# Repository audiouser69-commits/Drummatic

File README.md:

# Drummatic 0.4.0 — drum synth a 8 voci

Standalone per Windows (`Drummatic.exe` / `Drummatic.app`) e plugin VST3 (`Drummatic.vst3`) per Windows e macOS dallo stesso codice JUCE.
Architettura modellata sulle funzioni di una drum machine ibrida synth/sampler con sequencer euclideo;
nome, grafica e codice sono originali.

## Installazione
- **Standalone**: copia `Drummatic.exe` dove vuoi e avvialo. In *Options → Audio/MIDI Settings* scegli scheda audio
  (WASAPI/DirectSound) e, se vuoi, l'ingresso MIDI.
- **VST3 Windows**: copia `Drummatic.vst3` in `C:\Program Files\Common Files\VST3\` e riesegui la scansione in Ableton.
- **macOS**: `Drummatic.vst3` in `~/Library/Audio/Plug-Ins/VST3/`, `Drummatic.app` in Applicazioni; al primo avvio
  `xattr -dr com.apple.quarantine ~/Library/Audio/Plug-Ins/VST3/Drummatic.vst3 /Applications/Drummatic.app`.
- Preset, kit, campioni e WAV esportati vengono salvati in `Documenti/Drummatic/` (`Kits`, `Voices`, `Samples`, `Renders`); i file di `Documenti/Manipolo` vengono copiati lì al primo avvio.
  Con il pulsante **CARTELLA** nella barra superiore puoi scegliere un'altra cartella (anche un disco esterno), con la copia facoltativa dei file esistenti.
- Manuale completo: `docs/Drummatic-Manuale.pdf`.

## Funzioni
**Voce (×8)**
- Synth con 25 motori: Kick, Snare, Hat, Clap, FM, Modal, Cowbell, Zap, Pillow, Tripwire, Radiator, Kombucha
  (Karplus-Strong), LPG, Builder, Additive, Chaos, VOSIM, SumSyn, Reson, Combinatoric, Terraining, Shame, Entangled,
  Haywire, Scrapyard — PITCH + 4 manopole specifiche, ENV 2 come sorgente d'ampiezza, STEREO.
- Sampler con 4 motori: Classic (FINE, TILT, COMP, GAIN), Phase Warp (MIRROR, SHAPE, SPLIT, SWING),
  Cloner (FINE, TILT, VARIATION, DAMP — ogni colpo leggermente diverso; realizzato con un banco di 8 bande),
  Granular (SIZE, RATE, SPEED, BLUR). START/END trascinabili (END prima di START = reverse),
  drag & drop di WAV/AIFF/FLAC/OGG/MP3, file precedente/successivo/casuale nella cartella.
- BLEND synth/sampler (al 50% entrambi al massimo).
- TONE: 11 filtri (Scream/Dark LP-HP-BP, Comb FB±, FF±, AP), 11 distorsioni (Tape, Tube, Bitcrush, Rate Crush,
  Wavefold, Phase, Square, Dropout, MiniGlitch, MegaGlitch, Contrast), POST.
- Modulazione: RANDOM, VELOCITY, MACRO 1/2, ENV 1/2, LFO 1/2. Premi **MAP** su una sorgente e trascina le manopole
  per la profondità (doppio clic azzera). Tasto destro su una manopola = **lucchetto** (esclusa da VARIATION,
  randomizzazione e cambio preset). Alt+clic = valore di default.
- 2 inviluppi AHD (curva, velocity, soft reset), 2 LFO (Wavetable/Triangle Tilt/Pulse/Smooth Random,
  5 modalità di reset, sync o Hz fino a 440 Hz).
- VARIATION, mandate Delay/Reverb, PAN, VOICE GAIN; preset di voce, RESET, DADO.

**Sequencer per voce**
- Generatore euclideo STEPS/FILL/PATTERN (permutazioni)/ROTATE/INVERT + trigger manuali.
- SHIFT, SWING, SHAPE (accelera/rallenta), DENSITY; SPEED × MULT, LENGTH, SNAP, RESET; HUMANIZE globale condiviso.
- Lane per passo: VEL (127 = spinta extra di distorsione), SHIFT, PITCH, RATCH, ENV, PAN, VAR, PROB, SENDS, MACRO 2,
  ognuna con SYNC/FREE/TRIG/RETRIG e lunghezza propria; X, ruota ◀ ▶ (Alt = anche i trigger), DADO.
- Vista **ALL**: le sequenze delle 8 voci insieme, clic per aggiungere/togliere trigger, clic sul numero per selezionare la voce.
- Trasporto: segue il DAW, PLAY indipendente, STOP. In standalone usa il tempo in alto (BPM).
  Quando il DAW parte, il sequencer si riarma sempre, anche dopo uno STOP del plugin.

**Performance**
- ENV, SYNTH, SAMPLER, MODULATION (Macro 1/2, Variation, MOD AMP), TONE e SEQUENCER (Steps, Fill, Pattern, Density,
  Prob, Ratchet) agiscono su tutte le voci insieme.
- Per voce ENABLE e FLIP; GLOBAL con DEPTH bipolare, DADO (con profondità propria), COMMIT, RESET, ENABLED.
- Tasto destro su una manopola Performance la esclude dal DADO; i lucchetti delle voci la escludono dalla Performance.

**Mixer / FX / Master**
- Strip per voce con DELAY, REVERB, PAN, GAIN, TRIGGER (catena), CHOKE, ROUTING, Mute/Solo.
- **Uscite multiple**: Main 1-2 + 7 coppie stereo (3-4 … 15-16). In Ableton attiva le uscite del plugin e crea tracce
  audio con ingresso da Manipolo. Il MASTER agisce solo sul Main; le mandate FX escono sempre dal Main.
- Shatter Delay (tempo istantaneo senza glissati, GLITCH, STEREO, PONG, DUCKING, FB TILT, S.RATE, mandata al riverbero).
- Headspace Reverb (FDN, 4 modi, PREDELAY sync, DECAY, S.RATE, IN/OUT TILT).
- Master: MAXIMIZE, EQ 3 bande, Soft/Hard/Wavefold/No clip, GAIN.

**MIDI** (come da specifica)
- Ch 1: Do…Sol (qualsiasi ottava) = voci 1–8 · Ch 2–9: cromatico per voce (C3/60 = intonazione base)
- Ch 10: 0 play/stop, 1 play, 2 stop, 12–19 mute, 24–31 solo, 36–43 mute momentaneo, 48–55 solo momentaneo, 60–67 choke
- Ch 11: 0/1 kit prec./succ., 2 kit casuale, 3 randomizza tutto, 12 dado Performance, 13 reset Performance,
  14 commit Performance, 24–31 randomizza voce

**Tastiera** (pulsante TASTI attivo e finestra a fuoco): Q suona la voce, W/S voce su/giù, A/D pagina (VOICE/SEQ/MIX/PERFORM);
Spazio play/stop solo nello standalone. Nel DAW TASTI è spento di default, così spazio e tastiera MIDI del computer restano al DAW.
Shift+clic o doppio clic su una voce a sinistra = ascolto.

## Novità 0.4.0 — LAZER e performance di glitch programmate
**Cartella dei file selezionabile**: pulsante CARTELLA nella barra superiore (scegli, apri, torna a Documenti/Drummatic); copia facoltativa di kit, preset, campioni e WAV, con i percorsi dei campioni aggiornati nei kit copiati. Vale per standalone e plugin.

**Pagina LAZER** (nuova scheda, per la voce selezionata)
- Terzo strato sonoro accanto a synth e sampler: **64 motori glitch in 16 famiglie** — FM Metals, Laser Sweeps,
  Wavefold Zaps, Grain Clouds, Sub Thumps, Bit Zaps, Ring Mods, Noise Bursts, Comb Pings, Chirps, Formants,
  Glitch Steps, Data Corrupt, Phase Distort, Shimmer Drones, Static & Radio (4 varianti ciascuna).
- **12 manopole condivise** da tutti i motori (TUNE, SWEEP, S.TIME, TIMBRE, COLOR, MOD, RATE, GRIT, DENSITY, SPREAD,
  DECAY, LEVEL): ogni motore le interpreta a modo suo. Sono modulabili con MAP come le altre (LFO, inviluppi, macro,
  random, velocity), bloccabili e toccate da VARIATION e dal DADO.
- **Tappeti di fondo**: Grain Clouds, Shimmer Drones, Static & Radio e il Bowed Ping non ripartono da zero a ogni
  colpo; il tasto **ATMOSFERA** sceglie un motore di fondo con coda lunga e larga, da mettere sotto i glitch.
- Inviluppo proprio (DECAY fino a 20 s) oppure ENV 1 / ENV 2 della voce. Lo strato passa nel TONE della voce.
- **TAIL**: coda aggiunta a ogni colpo, 9 tipi (Bell, Metal, String, 808 Boom, Glass, Tube, Drone Pad, Noise Wash,
  Reverse Swell) con LEVEL, DECAY, TONE.
- **BRK TAPZ**: multi-tap fino a 32 ripetizioni; SHAPE accelera o rallenta i colpi (pallina che rimbalza), DECAY,
  SPREAD stereo, MIX, tempo sincronizzato o in ms.
- **BRK REPEAT**: stutter che registra una fetta del colpo e la ripete (REPEATS) con buchi casuali (GAPS), reverse
  e bitcrush casuali (CRUSH): fill spezzati.
- **KIT MODE**: sul canale MIDI della voce (2-9) ogni tasto suona un motore diverso (nota 36, C1 in Ableton = motore 1).
- **TRASCINA WAV**: trascina il colpo della voce direttamente nel DAW come file WAV (clic = salva nella
  cartella `Renders` di Drummatic).

**Sequencer della Performance** (pagina PERFORM)
- Fino a 64 passi a tempo col trasporto (durata del passo da 1/1 a 1/32T). Ogni passo può **bloccare** qualsiasi
  controllo Performance su un valore: è una scena programmata che cambia battuta dopo battuta.
- Nuovi controlli Performance per i glitch: LAZER (LEVEL, ENGINE, TIMBRE, COLOR, DENSITY, DECAY) e BRK (TZ MIX,
  TZ SHAPE, RPT MIX, GAPS, REVERSE, CRUSH). Un valore positivo su LEVEL / TZ MIX / RPT MIX **accende lo strato**
  anche nelle voci dove è spento: così un passo può far partire uno stutter o un laser solo lì.
- Per passo: **GLIDE** (scivola dalla scena precedente) e **PROB** (probabilità che il passo scatti).
- **REC**: in riproduzione i movimenti delle manopole vengono scritti nel passo che suona. **CATTURA** scrive le
  manopole nel passo selezionato; **Disegna**: scegli un controllo e disegna i valori passo per passo (Alt+clic
  toglie il blocco, tasto destro cancella il passo). **DADO GLITCH** genera una performance casuale (rispetta i
  lucchetti delle manopole).
- La sequenza si salva nel kit. Kit e preset delle versioni precedenti si caricano con lo strato LAZER spento.

**Hardware (Raspberry Pi)**: pagina VOICE con 4 banchi in più (LAZER 1/2, CODA E TAPZ, REPEAT) e pagina PERF con i
banchi GLITCH e GLITCH E SEQ. Il firmware FM-1 resta per ora alla versione precedente.

## Drummatic per M-VAVE FM-1
La cartella [`fm1/`](fm1/README.md) contiene Drummatic come **firmware per l'M-VAVE FM-1** (tutto tranne il sampler e
le uscite multiple: 8 voci, 25 motori, TONE, inviluppi, LFO, modulazione MAP, sequencer euclideo con le 10 lane,
Performance, delay, riverbero, master, MIDI) e un **emulatore nel browser** con lo stesso codice. Licenza GPL-3.0
(la piattaforma FM-1 viene da Felucca). Build: workflow *FM-1* di GitHub Actions (pacchetto `.fwsc`, emulatore,
Flasher per Windows).

## Drummatic hardware (Raspberry Pi 5) — novità 0.3.0
- Nuova app a schermo intero `drummatic-hw` per la macchina: Raspberry Pi 5 + Pisound + Touch Display 2 + circuito di controllo
  (cartella `hardware/`). Stesso motore audio del plugin.
- Il circuito "Drummatic Control" (USB-MIDI, canale 16) comanda 8 pagine (VOICE, SAMPLER, TONE, MOD, SEQ, LANE, MIX, PERF),
  8 encoder con banchi (frecce sinistra/destra), DATA, 16 tasti di passo, 8 tasti voce, trasporto, MAP, LOCK, DADO,
  COMMIT, KIT, COPY; i LED mostrano pagina, voce, passi e testina.
- Installazione: pacchetto `Drummatic-SD` (Raspberry Pi OS Lite 64 bit trixie + cartella `drummatic` sulla partizione bootfs),
  aggiornamenti, campioni e backup da chiavetta USB.
- Compilare: `cmake -S . -B build-a64 -G Ninja -DCMAKE_TOOLCHAIN_FILE=aarch64-toolchain.cmake -DDRUMMATIC_HW=ON`
  (sysroot con alsa-lib e freetype per aarch64), oppure nativo su Linux con `-DDRUMMATIC_HW=ON`.
  `DrummaticHWTest` simula il pannello e salva le schermate di tutte le pagine.

## Novità 0.2.4
- Risolto: l'audio poteva sparire all'improvviso dopo aver avviato Drummatic con il suo PLAY. Bastava che il DAW
  segnalasse anche per un attimo di essere in riproduzione (o partisse e si fermasse) perché il plugin passasse a
  "segui il DAW": al successivo stop del DAW restava muto finché non si premeva di nuovo PLAY. Ora il PLAY del plugin
  vale finché non premi STOP: col DAW in riproduzione segue la sua posizione, col DAW fermo continua da solo.
- Autoriparazione: se un motore, un filtro, una distorsione, il delay, il riverbero o il master producono un valore
  non valido, quel blocco viene azzerato al volo invece di restare guasto e zittire tutto.
- Diagnosi sullo schermo: se il sequencer è fermo mentre il DAW suona, al posto del nome del kit compare il motivo
  ("FERMO: premuto STOP" oppure "FERMO: nota MIDI … sul canale 10") e, dopo un'autoriparazione, "AUDIO RIPRISTINATO".

## Novità 0.2.3
- START ed END del sampler modulabili in modalità MAP trascinando i marcatori sulla forma d'onda (es. lane MACRO 2 → START per affettare un loop).
- Tempi visualizzati in modo pulito ("50 ms").
- Manuale: nuovo capitolo "Il sampler in pratica" con schermate annotate, grafici dei motori e sei tecniche.

## Novità 0.2.2
- Nuovo nome Drummatic, versione macOS universale, cartella utente `Documenti/Drummatic` con migrazione automatica.
- Corretta l'evidenziazione delle pagine nella barra superiore.

## Novità 0.2.1
- Risolto: l'audio poteva sparire durante la riproduzione nel DAW. Con la finestra del plugin attiva, lo spazio
  (e i tasti A/W/S/D della tastiera MIDI di Ableton) venivano catturati da Manipolo, che fermava il proprio sequencer.
  Ora i tasti restano al DAW e il play del DAW riarma comunque il sequencer.
- Un nuovo colpo annulla un CHOKE ancora in corso sulla stessa voce (prima poteva restare attenuata per un attimo).
- Distorsioni azzerate quando una voce riparte dal silenzio (Dropout non può più restare bloccato).
- Il DADO di voce/RANDOM non cambia più ROUTING ed ENABLE/FLIP della Performance (poteva mandare una voce
  su un'uscita ausiliaria non attiva, facendola sparire dal Main).
- Protezione contro blocchi audio più grandi di quelli annunciati dall'host.

## Limiti noti
- Driver **ASIO** non incluso nello standalone (l'SDK ASIO di Steinberg non è ridistribuibile): usa WASAPI in modalità
  esclusiva per una latenza bassa, oppure il VST3 dentro Ableton.
- La modulazione è calcolata ogni 16 campioni (≈0,3 ms): gli LFO fino a 440 Hz sono "audio-rate" solo in modo approssimato.
- Il Cloner usa un banco di filtri a 8 bande invece di una vera elaborazione FFT.
- Binari non firmati da un'autorità: Windows SmartScreen e macOS Gatekeeper mostrano un avviso al primo avvio.

## Compilare
Cross-compilazione da Linux: `cmake -S . -B build-win -G Ninja -DCMAKE_TOOLCHAIN_FILE=mingw-toolchain.cmake -DCMAKE_BUILD_TYPE=Release && cmake --build build-win`
(JUCE 7.0.12, scaricato automaticamente se manca la cartella `JUCE`). Su Windows funziona anche con Visual Studio 2022;
su macOS: `cmake -S . -B build -G Xcode -DCMAKE_OSX_ARCHITECTURES="arm64;x86_64" && cmake --build build --config Release`.
Test: `-DMANIPOLO_TESTS=ON` poi `ManipoloTest`.

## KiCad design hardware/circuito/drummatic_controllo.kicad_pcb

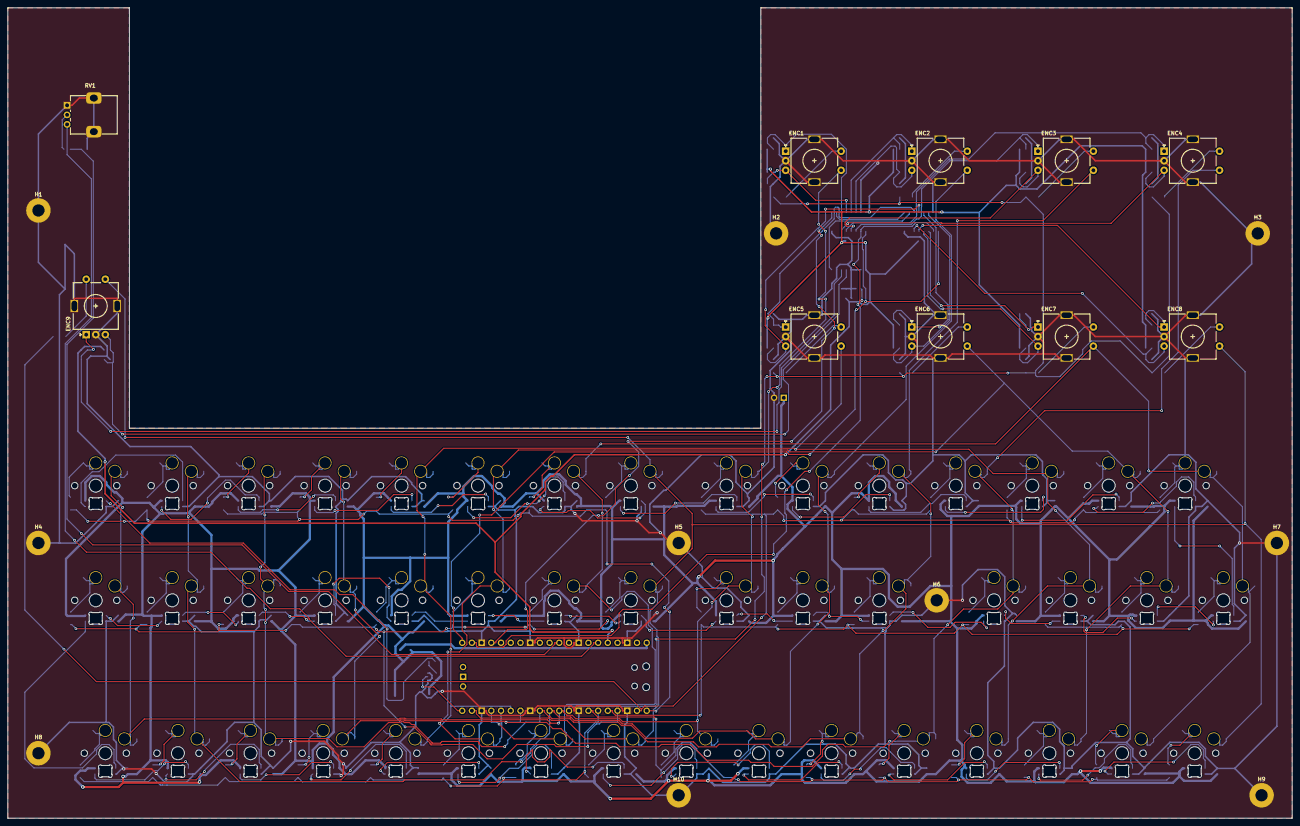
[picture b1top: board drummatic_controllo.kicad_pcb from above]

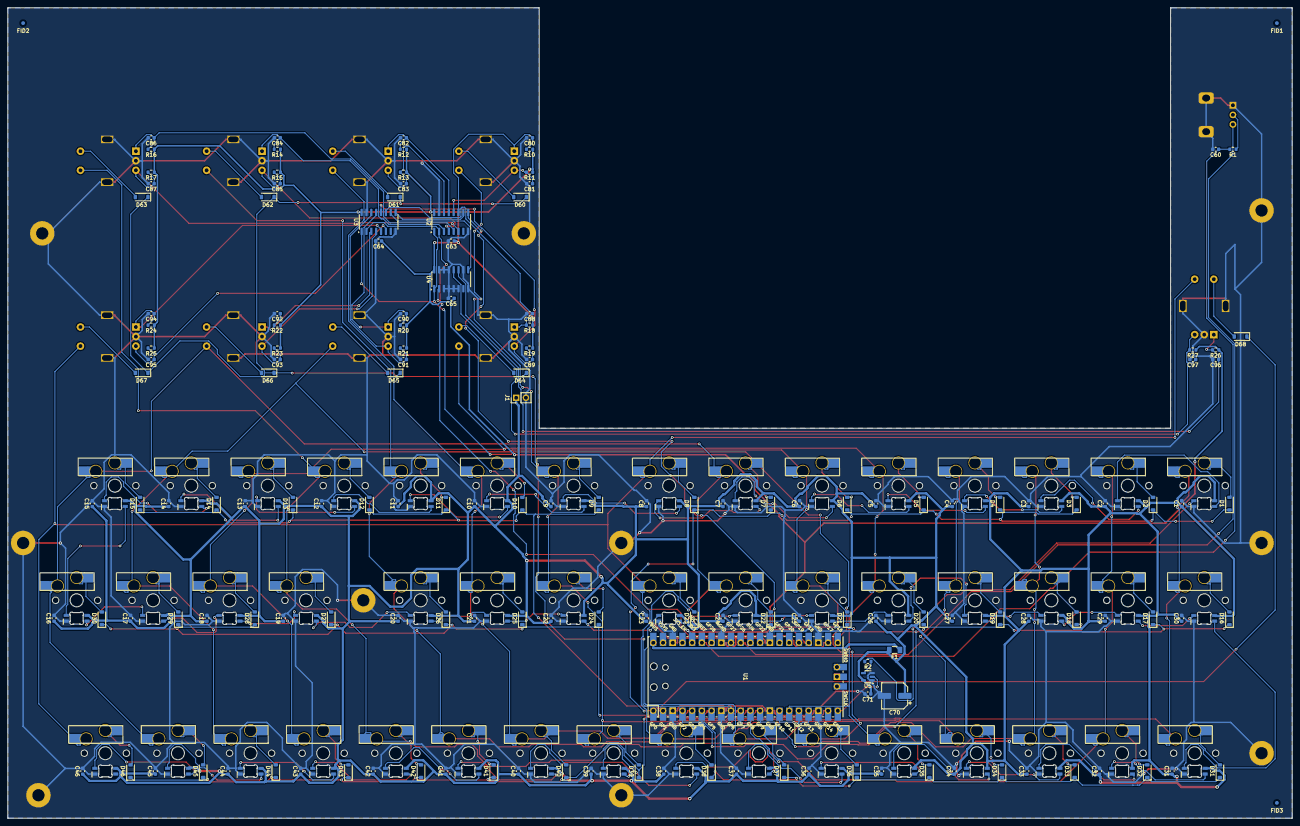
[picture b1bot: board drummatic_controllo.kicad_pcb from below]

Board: 2 copper layers, 336.0 x 212.0 mm, 267 parts (247 on the bottom side), 148 nets.

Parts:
C1, C2, C3, C4, C5, C6, C7, C8, C9, C10, C11, C12, C13, C14, C15, C16, C17, C18, C19, C20, C21, C22, C23, C24, C25, C26, C27, C28, C29, C30, C31, C32, C33, C34, C35, C36, C37, C38, C39, C40, C41, C42, C43, C44, C45, C46, C60, C63, C64, C65, C71: 100nF; C_0603_1608Metric
C70: 220uF 10V; CP_Elec_6.3x7.7
C80, C81, C82, C83, C84, C85, C86, C87, C88, C89, C90, C91, C92, C93, C94, C95, C96, C97: 10nF; C_0603_1608Metric
D1, D2, D3, D4, D5, D6, D7, D8, D9, D10, D11, D12, D13, D14, D15, D16, D17, D18, D19, D20, D21, D22, D23, D24, D25, D26, D27, D28, D29, D30, D31, D32, D33, D34, D35, D36, D37, D38, D39, D40, D41, D42, D43, D44, D45, D46, D60, D61, D62, D63, D64, D65, D66, D67, D68: 1N4148W; D_SOD-123
ENC1: EC11E ENC1; RotaryEncoder_Alps_EC11E-Switch_Vertical_H20mm
ENC2: EC11E ENC2; RotaryEncoder_Alps_EC11E-Switch_Vertical_H20mm
ENC3: EC11E ENC3; RotaryEncoder_Alps_EC11E-Switch_Vertical_H20mm
ENC4: EC11E ENC4; RotaryEncoder_Alps_EC11E-Switch_Vertical_H20mm
ENC5: EC11E ENC5; RotaryEncoder_Alps_EC11E-Switch_Vertical_H20mm
ENC6: EC11E ENC6; RotaryEncoder_Alps_EC11E-Switch_Vertical_H20mm
ENC7: EC11E ENC7; RotaryEncoder_Alps_EC11E-Switch_Vertical_H20mm
ENC8: EC11E ENC8; RotaryEncoder_Alps_EC11E-Switch_Vertical_H20mm
ENC9: EC11E DATA; RotaryEncoder_Alps_EC11E-Switch_Vertical_H20mm
F1: PTC 1.5A; Fuse_1206_3216Metric
FID1, FID2, FID3: Fiducial; Fiducial_1mm_Mask2mm
H1, H2, H3, H4, H5, H6, H7, H8, H9, H10: M3; MountingHole_3.2mm_M3_Pad
J1: DISPLAY 5V; PinHeader_1x02_P2.54mm_Vertical
LED1, LED2, LED3, LED4, LED5, LED6, LED7, LED8, LED9, LED10, LED11, LED12, LED13, LED14, LED15, LED16, LED17, LED18, LED19, LED20, LED21, LED22, LED23, LED24, LED25, LED26, LED27, LED28, LED29, LED30, LED31, LED32, LED33, LED34, LED35, LED36, LED37, LED38, LED39, LED40, LED41, LED42, LED43, LED44, LED45, LED46: SK6812MINI-E; SK6812MINI-E_Reverse
R1: 1k; R_0603_1608Metric
R2: 330R; R_0603_1608Metric
R10, R11, R12, R13, R14, R15, R16, R17, R18, R19, R20, R21, R22, R23, R24, R25, R26, R27: 10k; R_0603_1608Metric
RV1: 10k lin VOLUME; Potentiometer_Alps_RK09K_Single_Vertical
SW1: Choc v1 VOICE; Choc_v1_Hotswap
SW2: Choc v1 SMPL; Choc_v1_Hotswap
SW3: Choc v1 TONE; Choc_v1_Hotswap
SW4: Choc v1 MOD; Choc_v1_Hotswap
SW5: Choc v1 SEQ; Choc_v1_Hotswap
SW6: Choc v1 LANE; Choc_v1_Hotswap
SW7: Choc v1 MIX; Choc_v1_Hotswap
SW8: Choc v1 PERF; Choc_v1_Hotswap
SW9: Choc v1 FUNC; Choc_v1_Hotswap
SW10: Choc v1 MAP; Choc_v1_Hotswap
SW11: Choc v1 LOCK; Choc_v1_Hotswap
SW12: Choc v1 DADO; Choc_v1_Hotswap
SW13: Choc v1 COMMIT; Choc_v1_Hotswap
SW14: Choc v1 KIT; Choc_v1_Hotswap
SW15: Choc v1 COPY; Choc_v1_Hotswap
SW16: Choc v1 VOICE1; Choc_v1_Hotswap
SW17: Choc v1 VOICE2; Choc_v1_Hotswap
SW18: Choc v1 VOICE3; Choc_v1_Hotswap
SW19: Choc v1 VOICE4; Choc_v1_Hotswap
SW20: Choc v1 VOICE5; Choc_v1_Hotswap
SW21: Choc v1 VOICE6; Choc_v1_Hotswap
SW22: Choc v1 VOICE7; Choc_v1_Hotswap
SW23: Choc v1 VOICE8; Choc_v1_Hotswap
SW24: Choc v1 REC; Choc_v1_Hotswap
SW25: Choc v1 PLAY; Choc_v1_Hotswap
SW26: Choc v1 STOP; Choc_v1_Hotswap
SW27: Choc v1 LEFT; Choc_v1_Hotswap
SW28: Choc v1 UP; Choc_v1_Hotswap
SW29: Choc v1 DOWN; Choc_v1_Hotswap
SW30: Choc v1 RIGHT; Choc_v1_Hotswap
SW31: Choc v1 TRIG1; Choc_v1_Hotswap
SW32: Choc v1 TRIG2; Choc_v1_Hotswap
SW33: Choc v1 TRIG3; Choc_v1_Hotswap
SW34: Choc v1 TRIG4; Choc_v1_Hotswap
SW35: Choc v1 TRIG5; Choc_v1_Hotswap
SW36: Choc v1 TRIG6; Choc_v1_Hotswap
SW37: Choc v1 TRIG7; Choc_v1_Hotswap
SW38: Choc v1 TRIG8; Choc_v1_Hotswap
SW39: Choc v1 TRIG9; Choc_v1_Hotswap
SW40: Choc v1 TRIG10; Choc_v1_Hotswap
SW41: Choc v1 TRIG11; Choc_v1_Hotswap
SW42: Choc v1 TRIG12; Choc_v1_Hotswap
SW43: Choc v1 TRIG13; Choc_v1_Hotswap
SW44: Choc v1 TRIG14; Choc_v1_Hotswap
SW45: Choc v1 TRIG15; Choc_v1_Hotswap
SW46: Choc v1 TRIG16; Choc_v1_Hotswap
U1: Raspberry Pi Pico 2; RPi_Pico_SMD_TH
U2, U3, U4: 74HC165; SOIC-16_3.9x9.9mm_P1.27mm
U5: 74AHCT1G125; SOT-23-5

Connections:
+3V3: C63.1, C64.1, C65.1, R10.1, R11.1, R12.1, R13.1, R14.1, R15.1, R16.1, R17.1, R18.1, R19.1, R20.1, R21.1, R22.1, R23.1, R24.1, R25.1, R26.1, R27.1, U1.36, U2.16, U3.16, U4.16
+5V: C1.1, C2.1, C3.1, C4.1, C5.1, C6.1, C7.1, C8.1, C9.1, C10.1, C11.1, C12.1, C13.1, C14.1, C15.1, C16.1, C17.1, C18.1, C19.1, C20.1, C21.1, C22.1, C23.1, C24.1, C25.1, C26.1, C27.1, C28.1, C29.1, C30.1, C31.1, C32.1, C33.1, C34.1, C35.1, C36.1, C37.1, C38.1, C39.1, C40.1, C41.1, C42.1, C43.1, C44.1, C45.1, C46.1, C70.1, C71.1, F1.2, J1.1, LED1.1, LED2.1, LED3.1, LED4.1, LED5.1, LED6.1, LED7.1, LED8.1, LED9.1, LED10.1, LED11.1, LED12.1, LED13.1, LED14.1, LED15.1, LED16.1, LED17.1, LED18.1, LED19.1, LED20.1, LED21.1, LED22.1, LED23.1, LED24.1, LED25.1, LED26.1, LED27.1, LED28.1, LED29.1, LED30.1, LED31.1, LED32.1, LED33.1, LED34.1, LED35.1, LED36.1, LED37.1, LED38.1, LED39.1, LED40.1, LED41.1, LED42.1, LED43.1, LED44.1, LED45.1, LED46.1, U5.5
ADC0: C60.1, R1.2, U1.31
ADC_VREF: RV1.3, U1.35
COL0: ENC1.S1, SW1.1, SW9.1, SW16.1, SW24.1, SW31.1, SW39.1, U1.10
COL1: ENC2.S1, SW2.1, SW10.1, SW17.1, SW25.1, SW32.1, SW40.1, U1.11
COL2: ENC3.S1, SW3.1, SW11.1, SW18.1, SW26.1, SW33.1, SW41.1, U1.12
COL3: ENC4.S1, SW4.1, SW12.1, SW19.1, SW27.1, SW34.1, SW42.1, U1.14
COL4: ENC5.S1, SW5.1, SW13.1, SW20.1, SW28.1, SW35.1, SW43.1, U1.15
COL5: ENC6.S1, SW6.1, SW14.1, SW21.1, SW29.1, SW36.1, SW44.1, U1.16
COL6: ENC7.S1, SW7.1, SW15.1, SW22.1, SW30.1, SW37.1, SW45.1, U1.17
COL7: ENC8.S1, ENC9.S1, SW8.1, SW23.1, SW38.1, SW46.1, U1.19
DATA_A: C96.1, ENC9.A, R26.2, U4.11
DATA_B: C97.1, ENC9.B, R27.2, U4.12
ENC1_A: C80.1, ENC1.A, R10.2, U2.11
ENC1_B: C81.1, ENC1.B, R11.2, U2.12
ENC2_A: C82.1, ENC2.A, R12.2, U2.13
ENC2_B: C83.1, ENC2.B, R13.2, U2.14
ENC3_A: C84.1, ENC3.A, R14.2, U2.3
ENC3_B: C85.1, ENC3.B, R15.2, U2.4
ENC4_A: C86.1, ENC4.A, R16.2, U2.5
ENC4_B: C87.1, ENC4.B, R17.2, U2.6
ENC5_A: C88.1, ENC5.A, R18.2, U3.11
ENC5_B: C89.1, ENC5.B, R19.2, U3.12
ENC6_A: C90.1, ENC6.A, R20.2, U3.13
ENC6_B: C91.1, ENC6.B, R21.2, U3.14
ENC7_A: C92.1, ENC7.A, R22.2, U3.3
ENC7_B: C93.1, ENC7.B, R23.2, U3.4
ENC8_A: C94.1, ENC8.A, R24.2, U3.5
ENC8_B: C95.1, ENC8.B, R25.2, U3.6
GND: C1.2, C2.2, C3.2, C4.2, C5.2, C6.2, C7.2, C8.2, C9.2, C10.2, C11.2, C12.2, C13.2, C14.2, C15.2, C16.2, C17.2, C18.2, C19.2, C20.2, C21.2, C22.2, C23.2, C24.2, C25.2, C26.2, C27.2, C28.2, C29.2, C30.2, C31.2, C32.2, C33.2, C34.2, C35.2, C36.2, C37.2, C38.2, C39.2, C40.2, C41.2, C42.2, C43.2, C44.2, C45.2, C46.2, C60.2, C63.2, C64.2, C65.2, C70.2, C71.2, C80.2, C81.2, C82.2, C83.2, C84.2, C85.2, C86.2, C87.2, C88.2, C89.2, C90.2, C91.2, C92.2, C93.2, C94.2, C95.2, C96.2, C97.2, ENC1.C, ENC1.MP, ENC2.C, ENC2.MP, ENC3.C, ENC3.MP, ENC4.C, ENC4.MP, ENC5.C, ENC5.MP, ENC6.C, ENC6.MP, ENC7.C, ENC7.MP, ENC8.C, ENC8.MP, ENC9.C, ENC9.MP, H1.1, H2.1, H3.1, H4.1, H5.1, H6.1, H7.1, H8.1, H9.1, H10.1, J1.2, LED1.4, LED2.4, LED3.4, LED4.4, LED5.4, LED6.4, LED7.4, LED8.4, LED9.4, LED10.4, LED11.4, LED12.4, LED13.4, LED14.4, LED15.4, LED16.4, LED17.4, LED18.4, LED19.4, LED20.4, LED21.4, LED22.4, LED23.4, LED24.4, LED25.4, LED26.4, LED27.4, LED28.4, LED29.4, LED30.4, LED31.4, LED32.4, LED33.4, LED34.4, LED35.4, LED36.4, LED37.4, LED38.4, LED39.4, LED40.4, LED41.4, LED42.4, LED43.4, LED44.4, LED45.4, LED46.4, RV1.1, RV1.MP, U1.3, U1.8, U1.13, U1.18, U1.23, U1.28, U1.33, U1.38, U2.8, U2.15, U3.8, U3.15, U4.3, U4.4, U4.5, U4.6, U4.8, U4.10, U4.13, U4.14, U4.15, U5.1, U5.3
K1: D1.2, SW1.2
K2: D2.2, SW2.2
K3: D3.2, SW3.2
K4: D4.2, SW4.2
K5: D5.2, SW5.2
K6: D6.2, SW6.2
K7: D7.2, SW7.2
K8: D8.2, SW8.2
K9: D9.2, SW9.2
K10: D10.2, SW10.2
K11: D11.2, SW11.2
K12: D12.2, SW12.2
K13: D13.2, SW13.2
K14: D14.2, SW14.2
K15: D15.2, SW15.2
K16: D16.2, SW16.2
K17: D17.2, SW17.2
K18: D18.2, SW18.2
K19: D19.2, SW19.2
K20: D20.2, SW20.2
K21: D21.2, SW21.2
K22: D22.2, SW22.2
K23: D23.2, SW23.2
K24: D24.2, SW24.2
K25: D25.2, SW25.2
K26: D26.2, SW26.2
K27: D27.2, SW27.2
K28: D28.2, SW28.2
K29: D29.2, SW29.2
K30: D30.2, SW30.2
K31: D31.2, SW31.2
K32: D32.2, SW32.2
K33: D33.2, SW33.2
K34: D34.2, SW34.2
K35: D35.2, SW35.2
K36: D36.2, SW36.2
K37: D37.2, SW37.2
K38: D38.2, SW38.2
K39: D39.2, SW39.2
K40: D40.2, SW40.2
K41: D41.2, SW41.2
K42: D42.2, SW42.2
K43: D43.2, SW43.2
K44: D44.2, SW44.2
K45: D45.2, SW45.2
K46: D46.2, SW46.2
KE1: D60.2, ENC1.S2
KE2: D61.2, ENC2.S2
KE3: D62.2, ENC3.S2
KE4: D63.2, ENC4.S2
KE5: D64.2, ENC5.S2
KE6: D65.2, ENC6.S2
KE7: D66.2, ENC7.S2
KE8: D67.2, ENC8.S2
KE9: D68.2, ENC9.S2
LED_3V3: U1.20, U5.2
LED_5V: R2.1, U5.4
LED_D1: LED1.2, LED2.3
LED_D2: LED2.2, LED3.3
LED_D3: LED3.2, LED4.3
LED_D4: LED4.2, LED5.3
LED_D5: LED5.2, LED6.3
LED_D6: LED6.2, LED7.3
LED_D7: LED7.2, LED8.3
LED_D8: LED8.2, LED9.3
LED_D9: LED9.2, LED10.3
LED_D10: LED10.2, LED11.3
LED_D11: LED11.2, LED12.3
LED_D12: LED12.2, LED13.3
LED_D13: LED13.2, LED14.3
LED_D14: LED14.2, LED15.3
LED_D15: LED15.2, LED16.3
LED_D16: LED16.2, LED17.3
LED_D17: LED17.2, LED18.3
LED_D18: LED18.2, LED19.3
LED_D19: LED19.2, LED20.3
LED_D20: LED20.2, LED21.3
LED_D21: LED21.2, LED22.3
LED_D22: LED22.2, LED23.3
LED_D23: LED23.2, LED24.3
LED_D24: LED24.2, LED25.3
LED_D25: LED25.2, LED26.3
LED_D26: LED26.2, LED27.3
LED_D27: LED27.2, LED28.3
LED_D28: LED28.2, LED29.3
LED_D29: LED29.2, LED30.3
LED_D30: LED30.2, LED31.3
LED_D31: LED31.2, LED32.3
LED_D32: LED32.2, LED33.3
LED_D33: LED33.2, LED34.3
LED_D34: LED34.2, LED35.3
LED_D35: LED35.2, LED36.3
LED_D36: LED36.2, LED37.3
LED_D37: LED37.2, LED38.3
LED_D38: LED38.2, LED39.3
LED_D39: LED39.2, LED40.3
LED_D40: LED40.2, LED41.3
LED_D41: LED41.2, LED42.3
LED_D42: LED42.2, LED43.3
LED_D43: LED43.2, LED44.3
LED_D44: LED44.2, LED45.3
LED_D45: LED45.2, LED46.3
LED_DIN0: LED1.3, R2.2
POT_W: R1.1, RV1.2
ROW0: D1.1, D2.1, D3.1, D4.1, D5.1, D6.1, D7.1, D8.1, U1.1
ROW1: D9.1, D10.1, D11.1, D12.1, D13.1, D14.1, D15.1, D68.1, U1.2
ROW2: D16.1, D17.1, D18.1, D19.1, D20.1, D21.1, D22.1, D23.1, U1.4
ROW3: D24.1, D25.1, D26.1, D27.1, D28.1, D29.1, D30.1, U1.5
ROW4: D31.1, D32.1, D33.1, D34.1, D35.1, D36.1, D37.1, D38.1, U1.6
ROW5: D39.1, D40.1, D41.1, D42.1, D43.1, D44.1, D45.1, D46.1, U1.7
ROW6: D60.1, D61.1, D62.1, D63.1, D64.1, D65.1, D66.1, D67.1, U1.9
SR_CLK: U1.22, U2.2, U3.2, U4.2
SR_DATA: U1.24, U2.9
SR_LOAD: U1.21, U2.1, U3.1, U4.1
SR_S1: U2.10, U3.9
SR_S2: U3.10, U4.9
VBUS: F1.1, U1.40

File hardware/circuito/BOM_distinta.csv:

Quantità,Valore,Codice produttore,Footprint,Montaggio,Lato,Designatori
51,100nF,GRM188R71H104KA93D,C_0603_1608Metric,SMD,Bottom,C1 C2 C3 C4 C5 C6 C7 C8 C9 C10 C11 C12 C13 C14 C15 C16 C17 C18 C19 C20 C21 C22 C23 C24 C25 C26 C27 C28 C29 C30 C31 C32 C33 C34 C35 C36 C37 C38 C39 C40 C41 C42 C43 C44 C45 C46 C60 C63 C64 C65 C71
1,220uF 10V,Panasonic EEE-FK1A221P,CP_Elec_6.3x7.7,SMD,Bottom,C70
18,10nF,GRM188R71H103KA01D,C_0603_1608Metric,SMD,Bottom,C80 C81 C82 C83 C84 C85 C86 C87 C88 C89 C90 C91 C92 C93 C94 C95 C96 C97
55,1N4148W,1N4148W-7-F (Diodes Inc.),D_SOD-123,SMD,Bottom,D1 D2 D3 D4 D5 D6 D7 D8 D9 D10 D11 D12 D13 D14 D15 D16 D17 D18 D19 D20 D21 D22 D23 D24 D25 D26 D27 D28 D29 D30 D31 D32 D33 D34 D35 D36 D37 D38 D39 D40 D41 D42 D43 D44 D45 D46 D60 D61 D62 D63 D64 D65 D66 D67 D68
9,Encoder EC11E con pulsante,Alps EC11E15244G1 (o EC11E15244B2),RotaryEncoder_Alps_EC11E-Switch_Vertical_H20mm,THT,Top,ENC1 ENC2 ENC3 ENC4 ENC5 ENC6 ENC7 ENC8 ENC9
1,PTC 1.5A,Littelfuse 1206L150THYR,Fuse_1206_3216Metric,SMD,Bottom,F1
1,DISPLAY 5V,"Header 2 pin 2,54 mm",PinHeader_1x02_P2.54mm_Vertical,THT,Bottom,J1
46,SK6812MINI-E,SK6812MINI-E (Opsco),SK6812MINI-E_Reverse,SMD,Bottom,LED1 LED2 LED3 LED4 LED5 LED6 LED7 LED8 LED9 LED10 LED11 LED12 LED13 LED14 LED15 LED16 LED17 LED18 LED19 LED20 LED21 LED22 LED23 LED24 LED25 LED26 LED27 LED28 LED29 LED30 LED31 LED32 LED33 LED34 LED35 LED36 LED37 LED38 LED39 LED40 LED41 LED42 LED43 LED44 LED45 LED46
1,1k,RC0603FR-071KL,R_0603_1608Metric,SMD,Bottom,R1
1,330R,RC0603FR-07330RL,R_0603_1608Metric,SMD,Bottom,R2
18,10k,RC0603FR-0710KL,R_0603_1608Metric,SMD,Bottom,R10 R11 R12 R13 R14 R15 R16 R17 R18 R19 R20 R21 R22 R23 R24 R25 R26 R27
1,10k lin VOLUME,Alps RK09K1130A5R (10k B),Potentiometer_Alps_RK09K_Single_Vertical,THT,Top,RV1
46,Presa hot-swap Choc v1,Kailh CPG135001S30 (presa hot-swap),Choc_v1_Hotswap,SMD,Bottom,SW1 SW2 SW3 SW4 SW5 SW6 SW7 SW8 SW9 SW10 SW11 SW12 SW13 SW14 SW15 SW16 SW17 SW18 SW19 SW20 SW21 SW22 SW23 SW24 SW25 SW26 SW27 SW28 SW29 SW30 SW31 SW32 SW33 SW34 SW35 SW36 SW37 SW38 SW39 SW40 SW41 SW42 SW43 SW44 SW45 SW46
1,Raspberry Pi Pico 2,Raspberry Pi Pico 2 (SC1631),RPi_Pico_SMD_TH,SMD,Bottom,U1
3,74HC165,SN74HC165DR (TI),SOIC-16_3.9x9.9mm_P1.27mm,SMD,Bottom,U2 U3 U4
1,74AHCT1G125,SN74AHCT1G125DBVR (TI),SOT-23-5,SMD,Bottom,U5

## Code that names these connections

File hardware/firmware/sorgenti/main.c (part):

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
#define MIDI_CH      15          /* canale 16 */
#define FW_VERSION   2           /* 1 = 26/10/2026; 2 = 27/10/2026, aggiornabile via SysEx */
#define PIN_ROW0     0
#define PIN_COL0     7
#define PIN_LED      15
#define PIN_SR_LOAD  16
#define PIN_SR_CLK   17
#define PIN_SR_DATA  18
#define PIN_POT      26
#define MAX_LEVEL    51          /* 20 % del massimo: 46 LED bianchi ~0,35 A, così LED + display restano sotto 1 A dall'USB */

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
/* ---------------------------------------------------------------- matrice tasti */
static void matrix_init(void) {
    for (int r = 0; r < 7; r++) { gpio_init(PIN_ROW0 + r); gpio_set_dir(PIN_ROW0 + r, GPIO_IN); }
    for (int c = 0; c < 8; c++) { gpio_init(PIN_COL0 + c); gpio_set_dir(PIN_COL0 + c, GPIO_IN); gpio_pull_up(PIN_COL0 + c); }
}

static void matrix_scan(void) {
    for (int r = 0; r < 7; r++) {
        /* riga attiva = uscita bassa, le altre in alta impedenza; i diodi vanno da colonna a riga */
        gpio_set_dir(PIN_ROW0 + r, GPIO_OUT); gpio_put(PIN_ROW0 + r, 0);
        busy_wait_us_32(10);
        uint32_t cols = gpio_get_all();
        gpio_set_dir(PIN_ROW0 + r, GPIO_IN);
        for (int c = 0; c < 8; c++) {
            int k = MATRIX[r][c];
            if (k < 0) continue;
            bool pressed = !(cols & (1u << (PIN_COL0 + c)));
            if (pressed != key_state[k]) {
                if (++key_debounce[k] >= 5) {       /* 5 scansioni consecutive (~5 ms) */
                    key_state[k] = pressed; key_debounce[k] = 0;
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static const int8_t QDEC[16] = {0, -1, 1, 0, 1, 0, 0, -1, -1, 0, 0, 1, 0, 1, -1, 0};

static void sr_init(void) {
    gpio_init(PIN_SR_LOAD); gpio_set_dir(PIN_SR_LOAD, GPIO_OUT); gpio_put(PIN_SR_LOAD, 1);
    gpio_init(PIN_SR_CLK); gpio_set_dir(PIN_SR_CLK, GPIO_OUT); gpio_put(PIN_SR_CLK, 0);
    gpio_init(PIN_SR_DATA); gpio_set_dir(PIN_SR_DATA, GPIO_IN);
}

static uint32_t sr_read(void) {
    gpio_put(PIN_SR_LOAD, 0); busy_wait_us_32(1); gpio_put(PIN_SR_LOAD, 1); busy_wait_us_32(1);
    uint32_t v = 0;
    for (int i = 0; i < 24; i++) {
        v = (v << 1) | (gpio_get(PIN_SR_DATA) ? 1 : 0);
        gpio_put(PIN_SR_CLK, 1); busy_wait_us_32(1); gpio_put(PIN_SR_CLK, 0); busy_wait_us_32(1);
    }
    return v;   /* bit 23 = primo letto (posizione 0 della tabella) */
}
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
